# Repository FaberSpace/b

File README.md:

# Ceas digital(afisaj cu tuburi)
----
###Functii
* Afisaj ora/data
* Afisaj temperatura
* Conectare usb

---
###Status
- [ ] Hardware
  - [x] Schema logica
  - [x] Layout
  - [x] Schema simulare
  - [ ] Implementare
- [ ] Software
  - [x] Adunare resurse
  - [x] Functii de baza
  - [ ] Software matur
  
  ---
###Descriere hardware

-  Afisajul consta in 4 tuburi rusesti de tip IV-9 numitron: 2 pentru ora si 2 ore pentru minute. Fiecare tub are un afisaj cu 7 segmente de tip filament. Acestea se alimenteaza la tensiuni joase si au nevoie de aproximativ 20 mA pentru a lumina. 
- MAX7219 – driver-ul care controleaza afisajele cu 7 segmente; are cate o iesire pentru fiecare digit in parte; comunica cu uC prin interfata SPI
- DS1307 – Real time clock (RTC) – ne da ora in format BCD ; datele si adresele sunt transmise prin protocolul I2C
- LM75 – senzor IC  digital de temperatura; comunica cu uC prin protocolul I2C; senzorul masoara temperatura materialului semiconductor din interior
- HC-SR505 – sensor PIR (passive infrared sensor); masoara cantitatea de lumina IR radiata de obiectele din jurul sau. 
- uC – ATMEGA328P – uC pe 8 biti cu 32 pini
- MICRO-USB – (tip B) 
- 3 butoane: pentru functie (ceas/temperatura), ora si minute
- In layout am folosit un conector de 8 pini la care vor fi legate ulterior segmentele afisajelor si un conector de 4 pini pentru digiti. Am adoptat aceasta abordare pentru a ocupa cat mai putin spatiu pe placa avand in vedere ca elementele de afisaj sunt legate in paralel. Electronica se va afla in interiorul unei carcase.

----

###Referinte:
- [Biblioteca LedControl](http://playground.arduino.cc/Main/LedControl)
- [Biblioteca RTC](https://github.com/adafruit/RTClib)
- [Biblioteca LM75](https://github.com/thefekete/LM75)
- TBA

----

###Evolutie
 > TBA

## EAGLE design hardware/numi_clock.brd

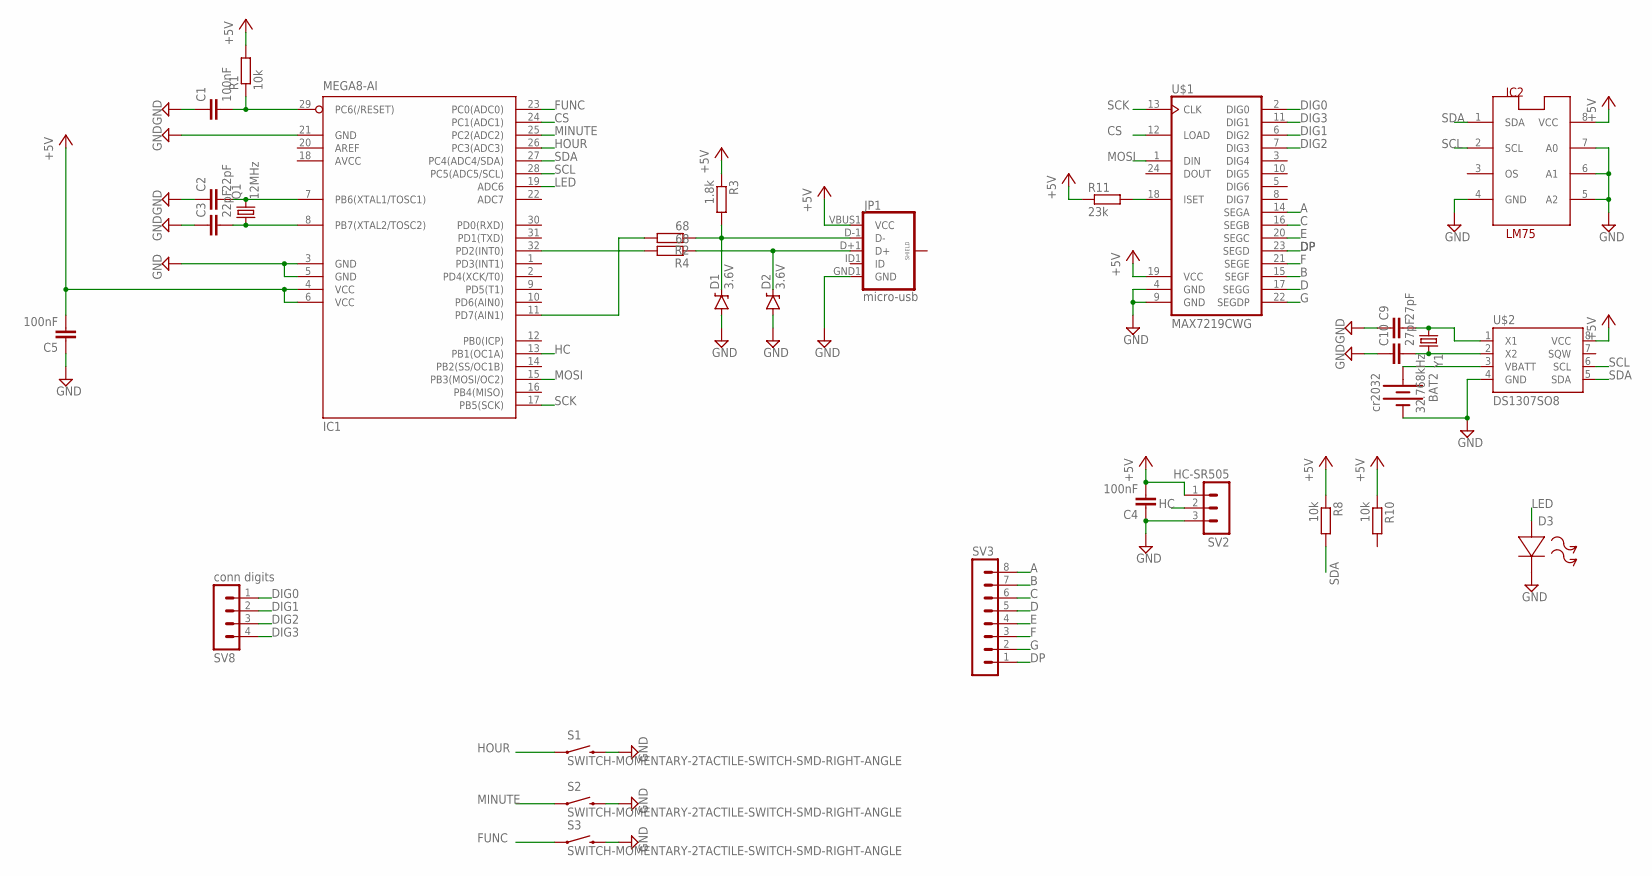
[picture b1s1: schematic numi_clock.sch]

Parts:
BAT2: cr2032; BATTCOM_20MM_PTH
C1, C4, C5: 100nF; C0805
C2, C3: 22pF; C0805
C9, C10: 27pF; C0805
D1, D2: 3.6V; SOD-323
D3: LED; R0805
IC1: MEGA8-AI; TQFP32-08
IC2: LM75; SO8_LM75
JP1: micro-usb; USB-B-MICRO-SMD_V03
Q1: 12MHz; CTS406
R1, R8, R10: 10k; R0805
R2, R4: 68; R0805
R3: 1.8k; R0805
R11: 23k; R0805
S1, S2, S3: SWITCH-MOMENTARY-2TACTILE-SWITCH-SMD-RIGHT-ANGLE; TACTILE_SWITCH-SMD-RIGHT-ANGLE
SV2: HC-SR505; MA03-1
SV3: MA08-1
SV8: conn digits; MA04-1
U$1: MAX7219CWG; SO24L
U$2: DS1307SO8; SO08
Y1: 32.768kHz; TC26H

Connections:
+5V: C4.2, C5.2, IC1.4 (VCC), IC1.6 (VCC), IC2.8 (VCC), JP1.VBUS1 (VCC), R1.2, R3.1, R8.1, R10.1, R11.1, SV2.1, U$1.19 (VCC), U$2.8 (VCC)
A: SV3.8, U$1.14 (SEGA)
AVCC: IC1.18 (AVCC)
B: SV3.7, U$1.15 (SEGF)
C: SV3.6, U$1.16 (SEGB)
CS: IC1.24 (PC1(ADC1)), U$1.12 (LOAD)
D: SV3.5, U$1.17 (SEGG)
DIG0: SV8.1, U$1.2 (DIG0)
DIG1: SV8.2, U$1.6 (DIG2)
DIG2: SV8.3, U$1.7 (DIG3)
DIG3: SV8.4, U$1.11 (DIG1)
DP: SV3.1, U$1.23 (SEGD)
E: SV3.4, U$1.20 (SEGC)
F: SV3.3, U$1.21 (SEGE)
FUNC: IC1.23 (PC0(ADC0)), S3.1
G: SV3.2, U$1.22 (SEGDP)
GND: BAT2.2 (-), C1.1, C2.1, C3.1, C4.1, C5.1, C9.1, C10.1, D1.A, D2.A, D3.2 (-), IC1.3 (GND), IC1.5 (GND), IC1.21 (GND), IC2.4 (GND), IC2.5 (A2), IC2.6 (A1), IC2.7 (A0), JP1.GND1 (GND), S1.2, S2.2, S3.2, SV2.3, U$1.4 (GND), U$1.9 (GND), U$2.4 (GND)
HC: IC1.13 (PB1(OC1A)), SV2.2
HOUR: IC1.26 (PC3(ADC3)), S1.1
LED: D3.1 (+), IC1.19 (ADC6)
MINUTE: IC1.25 (PC2(ADC2)), S2.1
MOSI: IC1.15 (PB3(MOSI/OC2)), U$1.1 (DIN)
unnamed: C2.2, IC1.7 (PB6(XTAL1/TOSC1)), Q1.3 (2)
unnamed: C3.2, IC1.8 (PB7(XTAL2/TOSC2)), Q1.1
unnamed: R11.2, U$1.18 (ISET)
unnamed: C9.2, U$2.1 (X1), Y1.1
unnamed: C10.2, U$2.2 (X2), Y1.2
unnamed: BAT2.1 (+), U$2.3 (VBATT)
unnamed: D2.C, JP1.D+1 (D+), R4.1
unnamed: D1.C, JP1.D-1 (D-), R2.1, R3.2
unnamed: IC1.32 (PD2(INT0)), R4.2
unnamed: IC1.11 (PD7(AIN1)), R2.2
RESET: C1.2, IC1.29 (PC6(/RESET)), R1.1
SCK: IC1.17 (PB5(SCK)), U$1.13 (CLK)
SCL: IC1.28 (PC5(ADC5/SCL)), IC2.2 (SCL), U$2.6 (SCL)
SDA: IC1.27 (PC4(ADC4/SDA)), IC2.1 (SDA), R8.2, U$2.5 (SDA)

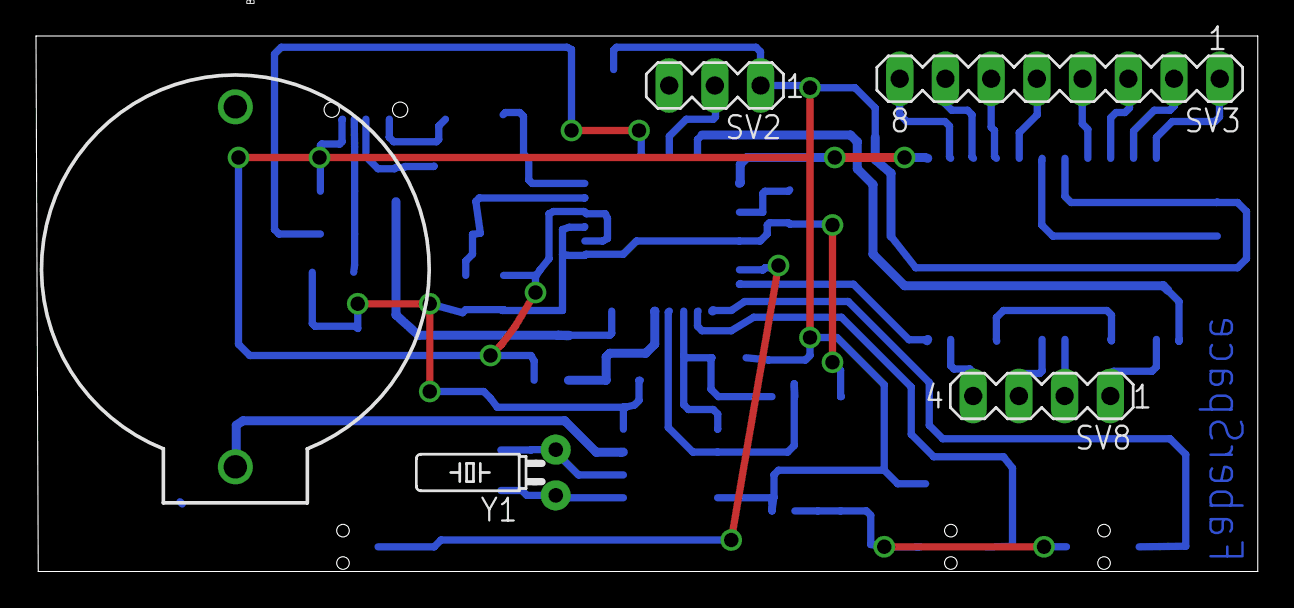
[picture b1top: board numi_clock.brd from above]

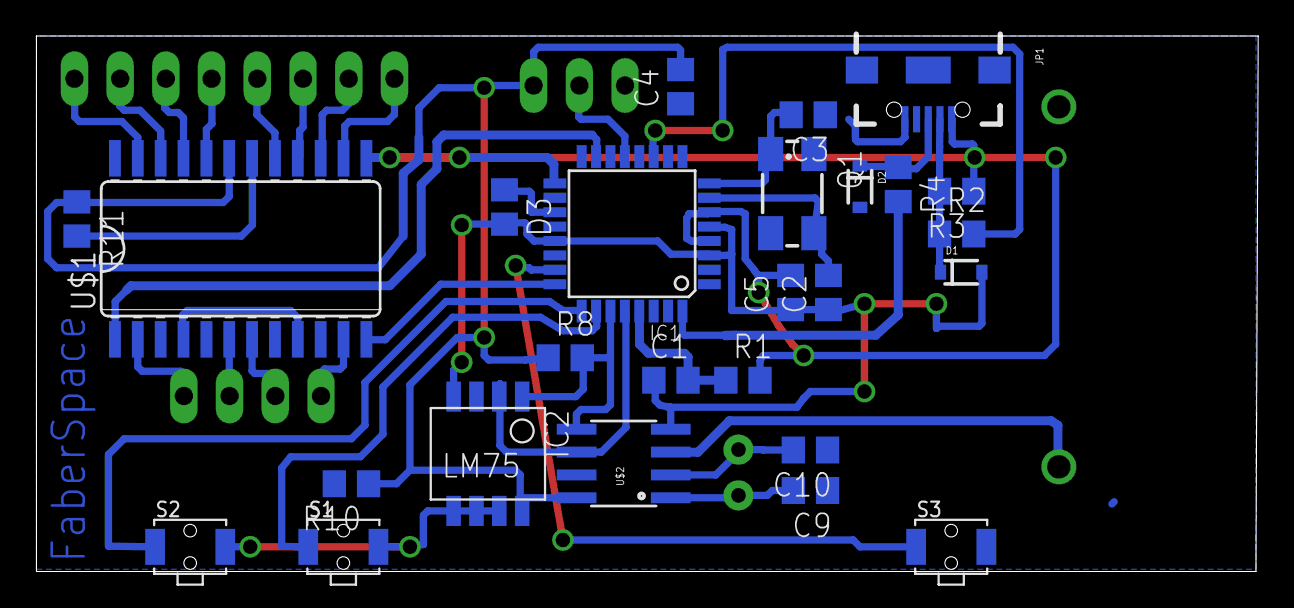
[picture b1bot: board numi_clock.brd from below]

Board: 2 copper layers, 67.8 x 29.7 mm, 31 parts (26 on the bottom side), 35 nets.

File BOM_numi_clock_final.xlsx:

Part | Value | Device | Package | Description | Link | Distribuitor | Pret
BAT2 | cr2032 | BATTERY20PTH | BATTCOM_20MM_PTH | Battery Holders
C1 | 100nF | C-EU0805 | 805 | CAPACITOR
C2 | 22pF | C-EU0805 | 805 | CAPACITOR
C3 | 22pF | C-EU0805 | 805 | CAPACITOR
C4 | 100nF | C-EU0805 | 805 | CAPACITOR
C5 | 100nF | C-EU0805 | 805 | CAPACITOR
C9 | 27pF | C-EU0805 | 805 | CAPACITOR
C10 | 27pF | C-EU0805 | 805 | CAPACITOR
D1 | 3.6V | DIODE-ZENER3.3V | SOD-323 | Zener Diode
D2 | 3.6V | DIODE-ZENER3.3V | SOD-323 | Zener Diode
D3 |  | LED | 805 | Light Emitting Diode
IC1 | ATMEGA328P | ATMEGA328P | TQFP32-08 | MICROCONTROLLER | (LINK) | Adelectrocom | 8.9
IC2 | LM75 | LM75_ICN | SO8_LM75 | Temperatursensor | (LINK) | Adelectrocom | 4.18
JP1 | micro-usb | USB_MICROB_PLUGCONN-11752 | USB-B-MICRO-SMD_V03 | USB Micro-B connectors
Q1 | 12MHz | CRYSTALCTS406 | CTS406 | CRYSTAL | (LINK) | Adelectrocom | 0.62
R1 | 10k | R-EU_0805 | 805 | RESISTOR | (LINK) | Adelectrocom | 0.05
R2 | 68 | R-EU_0805 | 805 | RESISTOR
R3 | 1.8k | R-EU_0805 | 805 | RESISTOR
R4 | 68 | R-EU_0805 | 805 | RESISTOR
R8 | 10k | R-EU_0805 | 805 | RESISTOR
R10 | 10k | R-EU_0805 | 805 | RESISTOR
R11 | 23k | R-EU_0805 | 805 | RESISTOR
S1 | SWITCH-MOMENTARY-2TACTILE-SWITCH-SMD-RIGHT-ANGLE | SWITCH-MOMENTARY-2TACTILE-SWITCH-SMD-RIGHT-ANGLE | TACTILE_SWITCH-SMD-RIGHT-ANGLE
S2 | SWITCH-MOMENTARY-2TACTILE-SWITCH-SMD-RIGHT-ANGLE | SWITCH-MOMENTARY-2TACTILE-SWITCH-SMD-RIGHT-ANGLE | TACTILE_SWITCH-SMD-RIGHT-ANGLE | Various NO switches- pushbuttons
S3 | SWITCH-MOMENTARY-2TACTILE-SWITCH-SMD-RIGHT-ANGLE | SWITCH-MOMENTARY-2TACTILE-SWITCH-SMD-RIGHT-ANGLE | TACTILE_SWITCH-SMD-RIGHT-ANGLE | Various NO switches- pushbuttons
SV2 | HC-SR505 | MA03-1 | MA03-1 | PIN HEADER
SV3 |  | MA08-1 | MA08-1 | PIN HEADER
SV8 | conn digits | MA04-1 | MA04-1 | PIN HEADER
U$1 | MAX7219CWG | MAX7219CWG | SO24L |  | (LINK) | Adelectrocom | 19.8
U$2 | DS1307SO8 | DS1307SO8 | SO08 | I2C real-time clock with battery backup. | (LINK) | Adelectrocom | 5.39
Y1 | 32.768kHz | CRYSTALTC26H | TC26H | Various standard crystals. Proven footprints.

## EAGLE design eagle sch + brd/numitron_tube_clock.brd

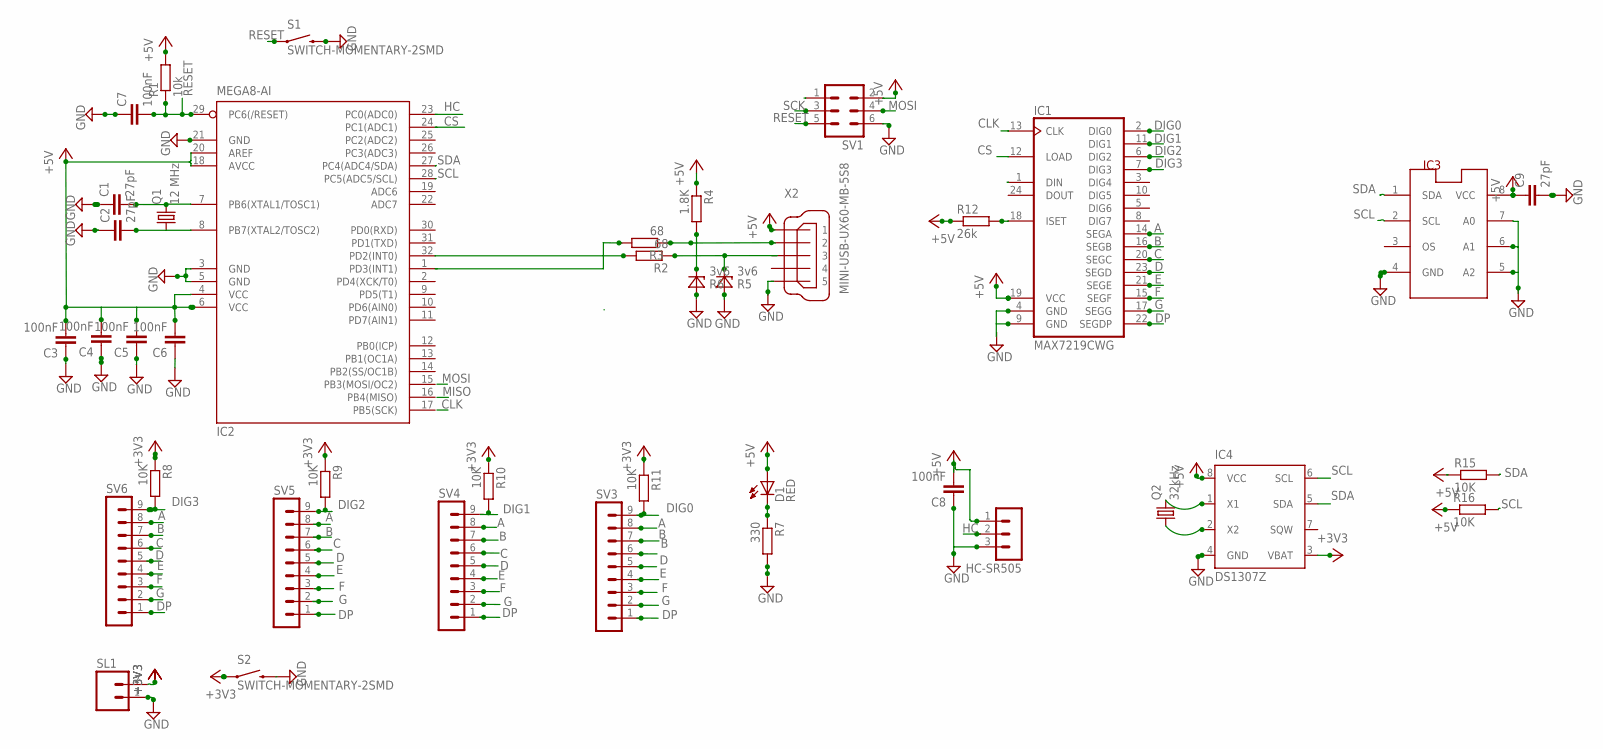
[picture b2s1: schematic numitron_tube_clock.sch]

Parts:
C1, C2, C9: 27pF; C0805
C3, C4, C5, C6, C7, C8: 100nF; C0805
D1: RED; HLMP6
HC-SR505: MA03-1
IC1: MAX7219CWG; SO24L
IC2: MEGA8-AI; TQFP32-08
IC3: LM75_ICN; SO8_LM75
IC4: DS1307Z; SOIC8
Q1: 12 MHz; HC49U-V
Q2: 32kHz; HC49U-V
R1: 10k; M0805
R2, R3: 68; M0805
R4: 1.8K; M0805
R5, R6: 3v6; Z-DIODE
R7: 330; M0805
R8, R9, R10, R11, R15, R16: 10K; M0805
R12: 26k; M0805
S1, S2: SWITCH-MOMENTARY-2SMD; TACTILE-SWITCH-SMD
SL1: MA02; 02PA
SV1: MA03-2
SV3, SV4, SV5, SV6: MA09-1
X2: MINI-USB-UX60-MB-5S8; UX60-MB-5S8

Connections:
+3V3: IC4.3 (VBAT), R11.1, S2.1
+5V: C3.2, C4.2, C5.2, C6.2, C8.2, D1.A, IC1.19 (VCC), IC2.6 (VCC), IC2.18 (AVCC), IC2.20 (AREF), IC4.8 (VCC), R4.1, R12.1, R15.1, R16.1, X2.1
A: IC1.14 (SEGA), SV3.8, SV4.8, SV5.8, SV6.8
B: IC1.16 (SEGB), SV3.7, SV4.7, SV5.7, SV6.7
C: IC1.20 (SEGC), SV4.6, SV5.6, SV6.6
CLK: IC1.13 (CLK)
CS: IC1.12 (LOAD), IC2.24 (PC1(ADC1))
D: IC1.23 (SEGD), SV3.5, SV4.5, SV5.5, SV6.5
DIG0: IC1.2 (DIG0), SV3.9
DIG1: IC1.11 (DIG1)
DIG2: IC1.6 (DIG2), SV5.9
DIG3: IC1.7 (DIG3), R8.2, SV6.9
DP: IC1.22 (SEGDP), SV3.1, SV4.1, SV5.1, SV6.1
E: IC1.21 (SEGE), SV3.4, SV4.4, SV5.4, SV6.4
F: IC1.15 (SEGF), SV3.3, SV4.3, SV5.3, SV6.3
G: IC1.17 (SEGG), SV3.2, SV4.2, SV5.2, SV6.2
GND: C1.1, C3.1, C4.1, C5.1, C6.1, C7.1, C8.1, C9.2, HC-SR505.3, IC2.3 (GND), IC2.5 (GND), IC2.21 (GND), IC3.6 (A1), IC3.7 (A0), IC4.4 (GND), R5.A, R7.2, S1.3 (2), S2.3 (2), SL1.1, SV1.6
HC: HC-SR505.2, IC2.23 (PC0(ADC0))
MISO: SV1.1
MOSI: IC1.1 (DIN), SV1.4
unnamed: C1.2, Q1.2
unnamed: C2.2, Q1.1
unnamed: R2.1, X2.3
unnamed: R3.1, R4.2, X2.2
unnamed: IC2.32 (PD2(INT0)), R2.2
unnamed: C9.1, IC3.8 (VCC)
unnamed: IC1.18 (ISET), R12.2
unnamed: D1.K, R7.1
unnamed: IC4.2 (X2), Q2.1
unnamed: IC4.1 (X1), Q2.2
unnamed: IC1.4 (GND), IC1.9 (GND)
RESET: C7.2, IC2.29 (PC6(/RESET)), SV1.5
SCK: SV1.3
SCL: IC2.28 (PC5(ADC5/SCL)), IC3.2 (SCL), IC4.6 (SCL), R16.2
SDA: IC2.27 (PC4(ADC4/SDA)), IC3.1 (SDA), IC4.5 (SDA), R15.2

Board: 2 copper layers, 40 parts (0 on the bottom side), 31 nets, no tracks yet.

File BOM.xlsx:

Part | Value | Device | Package | Description | MPN | Link |  | Lei
C1 | 27pF | C-EUC0805 | C0805 | CAPACITOR
C2 | 27pF | C-EUC0805 | C0805 | CAPACITOR
C3 | 100nF | C-EUC0805 | C0805 | CAPACITOR
C4 | 100nF | C-EUC0805 | C0805 | CAPACITOR
C5 | 100nF | C-EUC0805 | C0805 | CAPACITOR
C6 | 100nF | C-EUC0805 | C0805 | CAPACITOR
C7 | 100nF | C-EUC0805 | C0805 | CAPACITOR
C8 | 100nF | C-EUC0805 | C0805 | CAPACITOR
D1 | RED | HLMP6 | HLMP6 | LED | HLMP-6500
HC-SR505 |  | MA03-1 | MA03-1 | PIN HEADER
IC1 | MAX7219CNG | MAX7219CNG | DIL24-3 | LED DISPLAY DRIVER | MAX7219CNG | (LINK) | Adelectrocom | 19.8 | SOIC24
IC2 | MEGA8-AI | MEGA8-AI | TQFP32-08 | MICROCONTROLLER | ATMEGA8-16AU | (LINK) | Adelectrocom | 8.9
Q1 | 12 MHz | CRYSTALHC49U-V | HC49U-V | CRYSTAL |  | (LINK) | Adelectrocom | 0.62
Q2 | 12 MHz | CRYSTALHC49U-V | HC49U-V | CRYSTAL
R1 | 10k | R-EU_M0805 | M0805 | RESISTOR |  | (LINK) | Adelectrocom | 0.05
R2 | 68 | R-EU_M0805 | M0805 | RESISTOR |  | (LINK) | Adelectrocom | 0.05
R3 | 68 | R-EU_M0805 | M0805 | RESISTOR |  | (LINK) | Adelectrocom | 0.05
R4 | 1.8K | R-EU_M0805 | M0805 | RESISTOR
R5 | 3v6 | Z-DIODE | Z-DIODE | Z-Diode |  | (LINK) | Adelectrocom
R6 | 3v6 | Z-DIODE | Z-DIODE | Z-Diode |  | (LINK) | Adelectrocom
R7 | 330 | R-EU_M0805 | M0805 | RESISTOR |  | (LINK) | Adelectrocom | 0.05
R8 | 10K | R-EU_M0805 | M0805 | RESISTOR
R9 | 10K | R-EU_M0805 | M0805 | RESISTOR
R10 | 10K | R-EU_M0805 | M0805 | RESISTOR
R11 | 10K | R-EU_M0805 | M0805 | RESISTOR
R12 | 40k | R-EU_M0805 | M0805 | RESISTOR
SV1 |  | MA03-2 | MA03-2 | PIN HEADER
SV3 |  | MA09-1 | MA09-1 | PIN HEADER
SV4 |  | MA09-1 | MA09-1 | PIN HEADER
SV5 |  | MA09-1 | MA09-1 | PIN HEADER
SV6 |  | MA09-1 | MA09-1 | PIN HEADER
U$1 | DS1307 | DS1307 | DS1307 |  |  | (LINK) | Adelectrocom | 5.39 | SO8
X1 |  | USB-A003 | USB-A003 | USB connector |  | (LINK) | Adelectrocom | 0.82
 | LM75A |  |  |  |  | (LINK) | Adelectrocom | 4.18 | SOP8

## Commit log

2015-10-01 added sch file for numi clock
    eagle sch file
2015-10-02 create gitignore
    added proper gitignore for current project
2015-10-02 Fixes #2
    Fixes #2
2015-10-02 deleted unnecesarry files
    unnecesarry eagle files
2015-10-02 made folders
    made folders
2015-10-02 added BOM
    added BOM
2015-10-02 added power button and generated board
    added power button and generated board
2015-10-03 Fixes #1
    Fixes #1
2015-10-03 added buttons for hour, minute, function
    added buttons for hour, minute, function
2015-10-03 minor changes
    minor changes
2015-10-07 layout adjustments
    layout adjustments
2015-10-18 later edit
    later edit
2015-10-18 routed all tracks
    routed all tracks
2015-10-20 first software upload
    restructured directory tree, commit barebone max7219 example
2015-10-20 added proper libraries for all the functions
2015-10-26 added simulation
2015-10-26 software addition
2015-10-27 added references
2015-10-27 fixed typo
2015-11-03 updated README
    updated README
2015-11-05 rerouted some tracks
    rerouted some tracks
2015-12-05 added final BOM
    added final BOM

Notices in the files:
parts and their libraries:
SparkFun-DiscreteSemi: Licensing: Creative Commons ShareAlike 4.0 International - https://creativecommons.org/licenses/by-sa/4.0
SparkFun: Licensing: CC v3.0 Share-Alike You are welcome to use this library for commercial purposes.
